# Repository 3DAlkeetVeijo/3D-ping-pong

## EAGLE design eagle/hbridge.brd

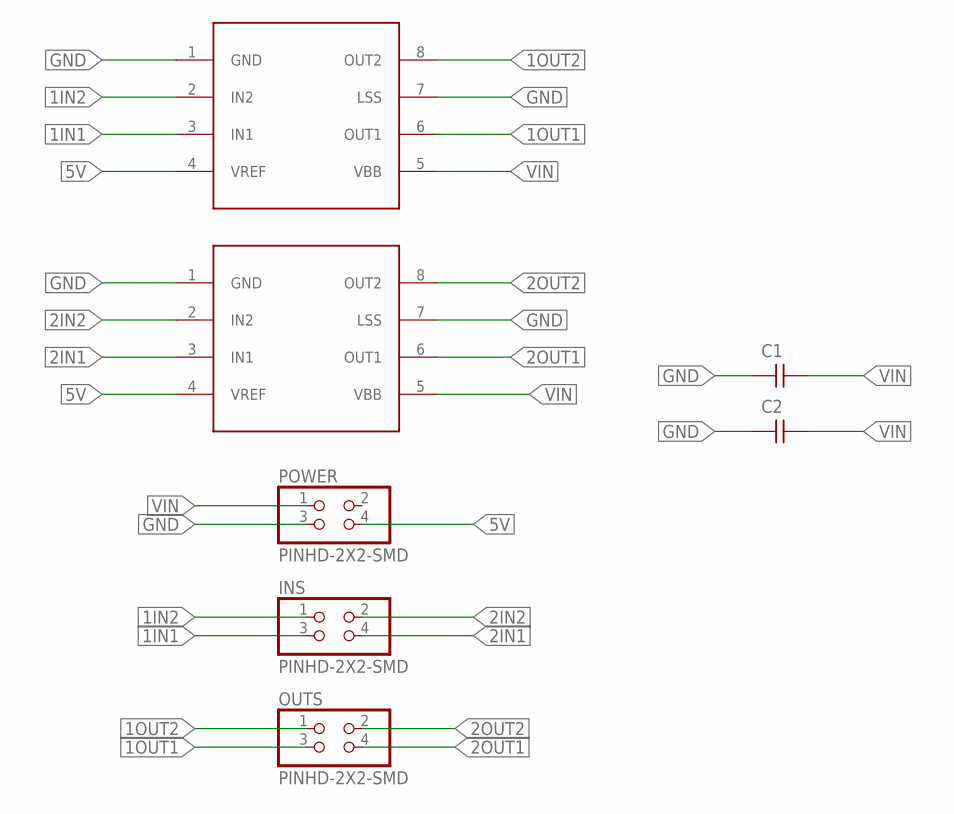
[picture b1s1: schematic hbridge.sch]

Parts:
C1, C2: CAP-UNPOLARIZEDFAB; C1206FAB
INS: PINHD-2X2-SMD; 2X02SMD
OUTS: PINHD-2X2-SMD; 2X02SMD
POWER: PINHD-2X2-SMD; 2X02SMD
U$1, U$2: A4953-H-BRIDGE-MOTOR-DRIVER; SOIC8

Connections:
1IN1: INS.3, U$1.3 (IN1)
1IN2: INS.1, U$1.2 (IN2)
1OUT1: OUTS.3, U$1.6 (OUT1)
1OUT2: OUTS.1, U$1.8 (OUT2)
2IN1: INS.4, U$2.3 (IN1)
2IN2: INS.2, U$2.2 (IN2)
2OUT1: OUTS.4, U$2.6 (OUT1)
2OUT2: OUTS.2, U$2.8 (OUT2)
5V: POWER.4, U$1.4 (VREF), U$2.4 (VREF)
GND: C1.1, C2.1, POWER.3, U$1.1 (GND), U$1.7 (LSS), U$2.1 (GND), U$2.7 (LSS)
VIN: C1.2, C2.2, POWER.1, U$1.5 (VBB), U$2.5 (VBB)

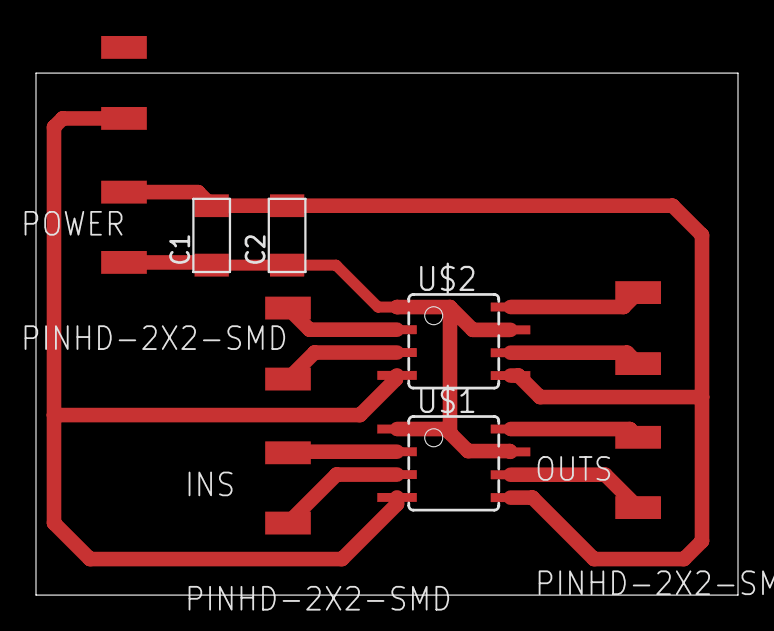
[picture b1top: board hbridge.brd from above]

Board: 2 copper layers, 39.0 x 29.0 mm, 7 parts (0 on the bottom side), 11 nets.

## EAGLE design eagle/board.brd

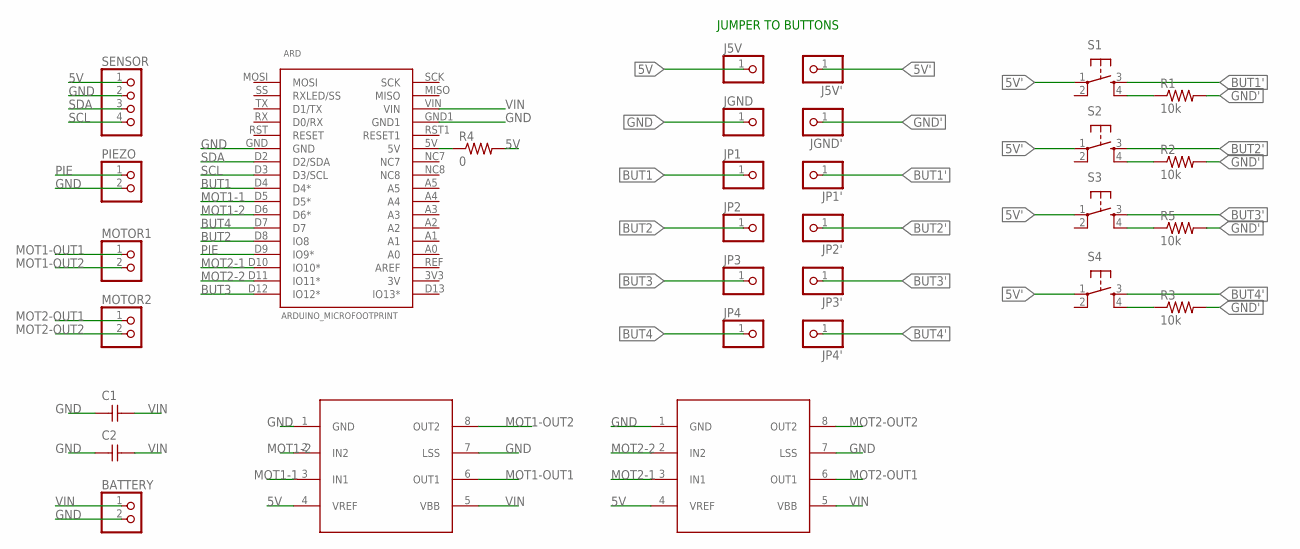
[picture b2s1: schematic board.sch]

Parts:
ARD: ARDUINO_MICROFOOTPRINT; ARDUINO-MICRO
BATTERY: PINHD-1X2; 1X02
C1, C2: CAP-UNPOLARIZEDFAB; C1206FAB
J5V, J5V': PINHD-1X1; 1X01
JGND: PINHD-1X1; 1X01
JGND': PINHD-1X1; 1X01
JP1, JP1', JP2, JP2', JP3, JP3', JP4, JP4': PINHD-1X1; 1X01
MOT1, MOT2: A4953-H-BRIDGE-MOTOR-DRIVER; SOIC8
MOTOR1, MOTOR2: PINHD-1X2; 1X02
PIEZO: PINHD-1X2; 1X02
R1, R2, R3, R5: 10k; R1206FAB
R4: 0; R1206FAB
S1, S2, S3, S4: 6MM_SWITCH6MM_SWITCH; 6MM_SWITCH
SENSOR: PINHD-1X4; 1X04

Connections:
5V: J5V.1, MOT1.4 (VREF), MOT2.4 (VREF), R4.2, SENSOR.1
5V': J5V'.1, S1.1, S2.1, S3.1, S4.1
BUT1: ARD.D4 (D4*), JP1.1
BUT1': JP1'.1, S1.3 (S)
BUT2: ARD.D8 (IO8), JP2.1
BUT2': JP2'.1, S2.3 (S)
BUT3: ARD.D12 (IO12*), JP3.1
BUT3': JP3'.1, S3.3 (S)
BUT4: ARD.D7, JP4.1
BUT4': JP4'.1, S4.3 (S)
GND: ARD.GND, ARD.GND1, BATTERY.2, C1.1, C2.1, JGND.1, MOT1.1 (GND), MOT1.7 (LSS), MOT2.1 (GND), MOT2.7 (LSS), PIEZO.2, SENSOR.2
GND': JGND'.1, R1.2, R2.2, R3.2, R5.2
MOT1-1: ARD.D5 (D5*), MOT1.3 (IN1)
MOT1-2: ARD.D6 (D6*), MOT1.2 (IN2)
MOT1-OUT1: MOT1.6 (OUT1), MOTOR1.1
MOT1-OUT2: MOT1.8 (OUT2), MOTOR1.2
MOT2-1: ARD.D10 (IO10*), MOT2.3 (IN1)
MOT2-2: ARD.D11 (IO11*), MOT2.2 (IN2)
MOT2-OUT1: MOT2.6 (OUT1), MOTOR2.1
MOT2-OUT2: MOT2.8 (OUT2), MOTOR2.2
unnamed: R3.1, S4.4 (S1)
unnamed: ARD.5V, R4.1
unnamed: R1.1, S1.4 (S1)
unnamed: R2.1, S2.4 (S1)
unnamed: R5.1, S3.4 (S1)
PIE: ARD.D9 (IO9*), PIEZO.1
SCL: ARD.D3 (D3/SCL), SENSOR.4
SDA: ARD.D2 (D2/SDA), SENSOR.3
VIN: ARD.VIN, BATTERY.1, C1.2, C2.2, MOT1.5 (VBB), MOT2.5 (VBB)

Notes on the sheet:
JUMPER TO BUTTONS

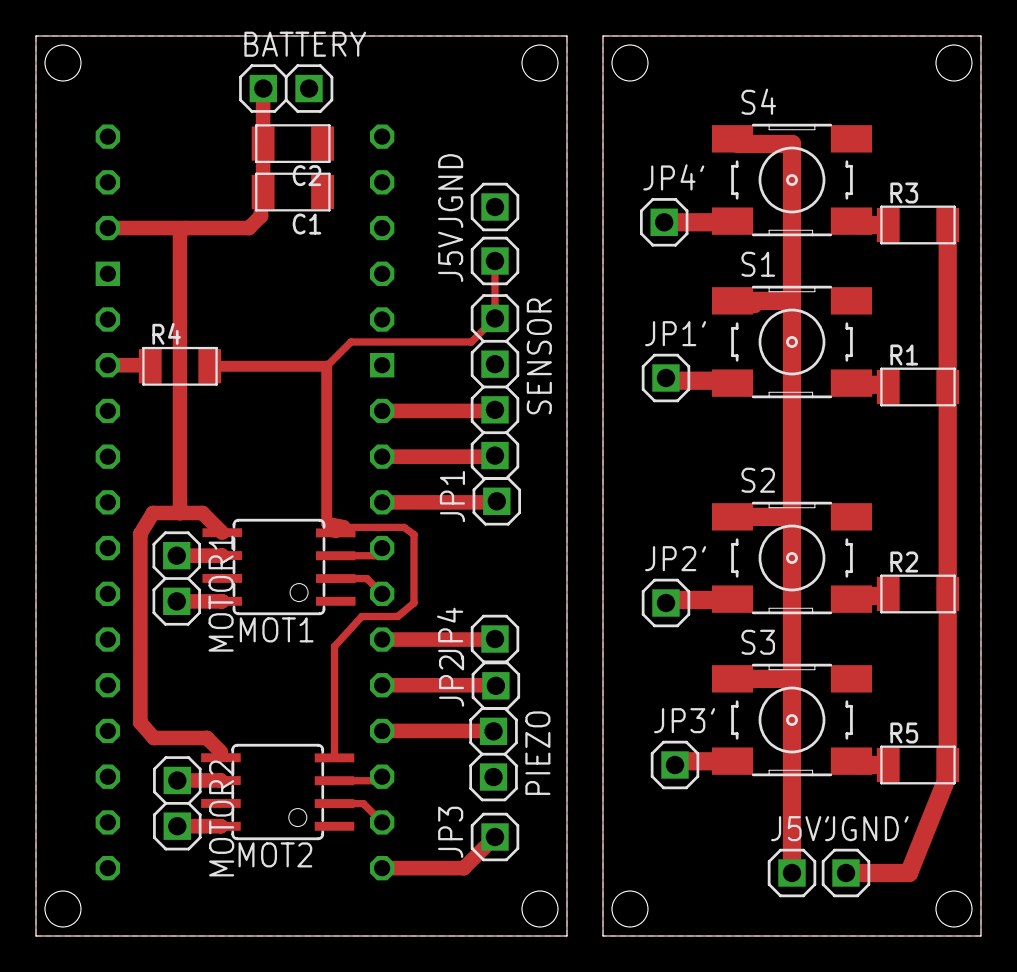
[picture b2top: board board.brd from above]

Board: 8 copper layers, 52.5 x 50.0 mm, 31 parts (1 on the bottom side), 29 nets.

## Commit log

2016-04-16 Create gh-pages branch via GitHub
2016-05-03 eagle pcb files
2016-05-03 eagle libraries
2016-05-05 pcb update
2016-05-05 Added files via upload
2016-05-05 the first version of the code
2016-05-05 added new picture
2016-05-12 h-bridge pcb files
2016-05-12 pcb milling png files
2016-06-22 uploaded photos of the measurements
2016-06-22 updated the github-pages
2016-06-24 added an 8th stage, with pictures of the hand drawn blueprints
2016-06-24 changed the name of the stage from 7th to 8th
2016-06-24 added the pictures to the 8th stage
2016-06-26 Added first proper version of the larger engine holder
2016-06-26 Added a new version of engine holder with imo more suitable measurements
2016-08-24 Added some old models
